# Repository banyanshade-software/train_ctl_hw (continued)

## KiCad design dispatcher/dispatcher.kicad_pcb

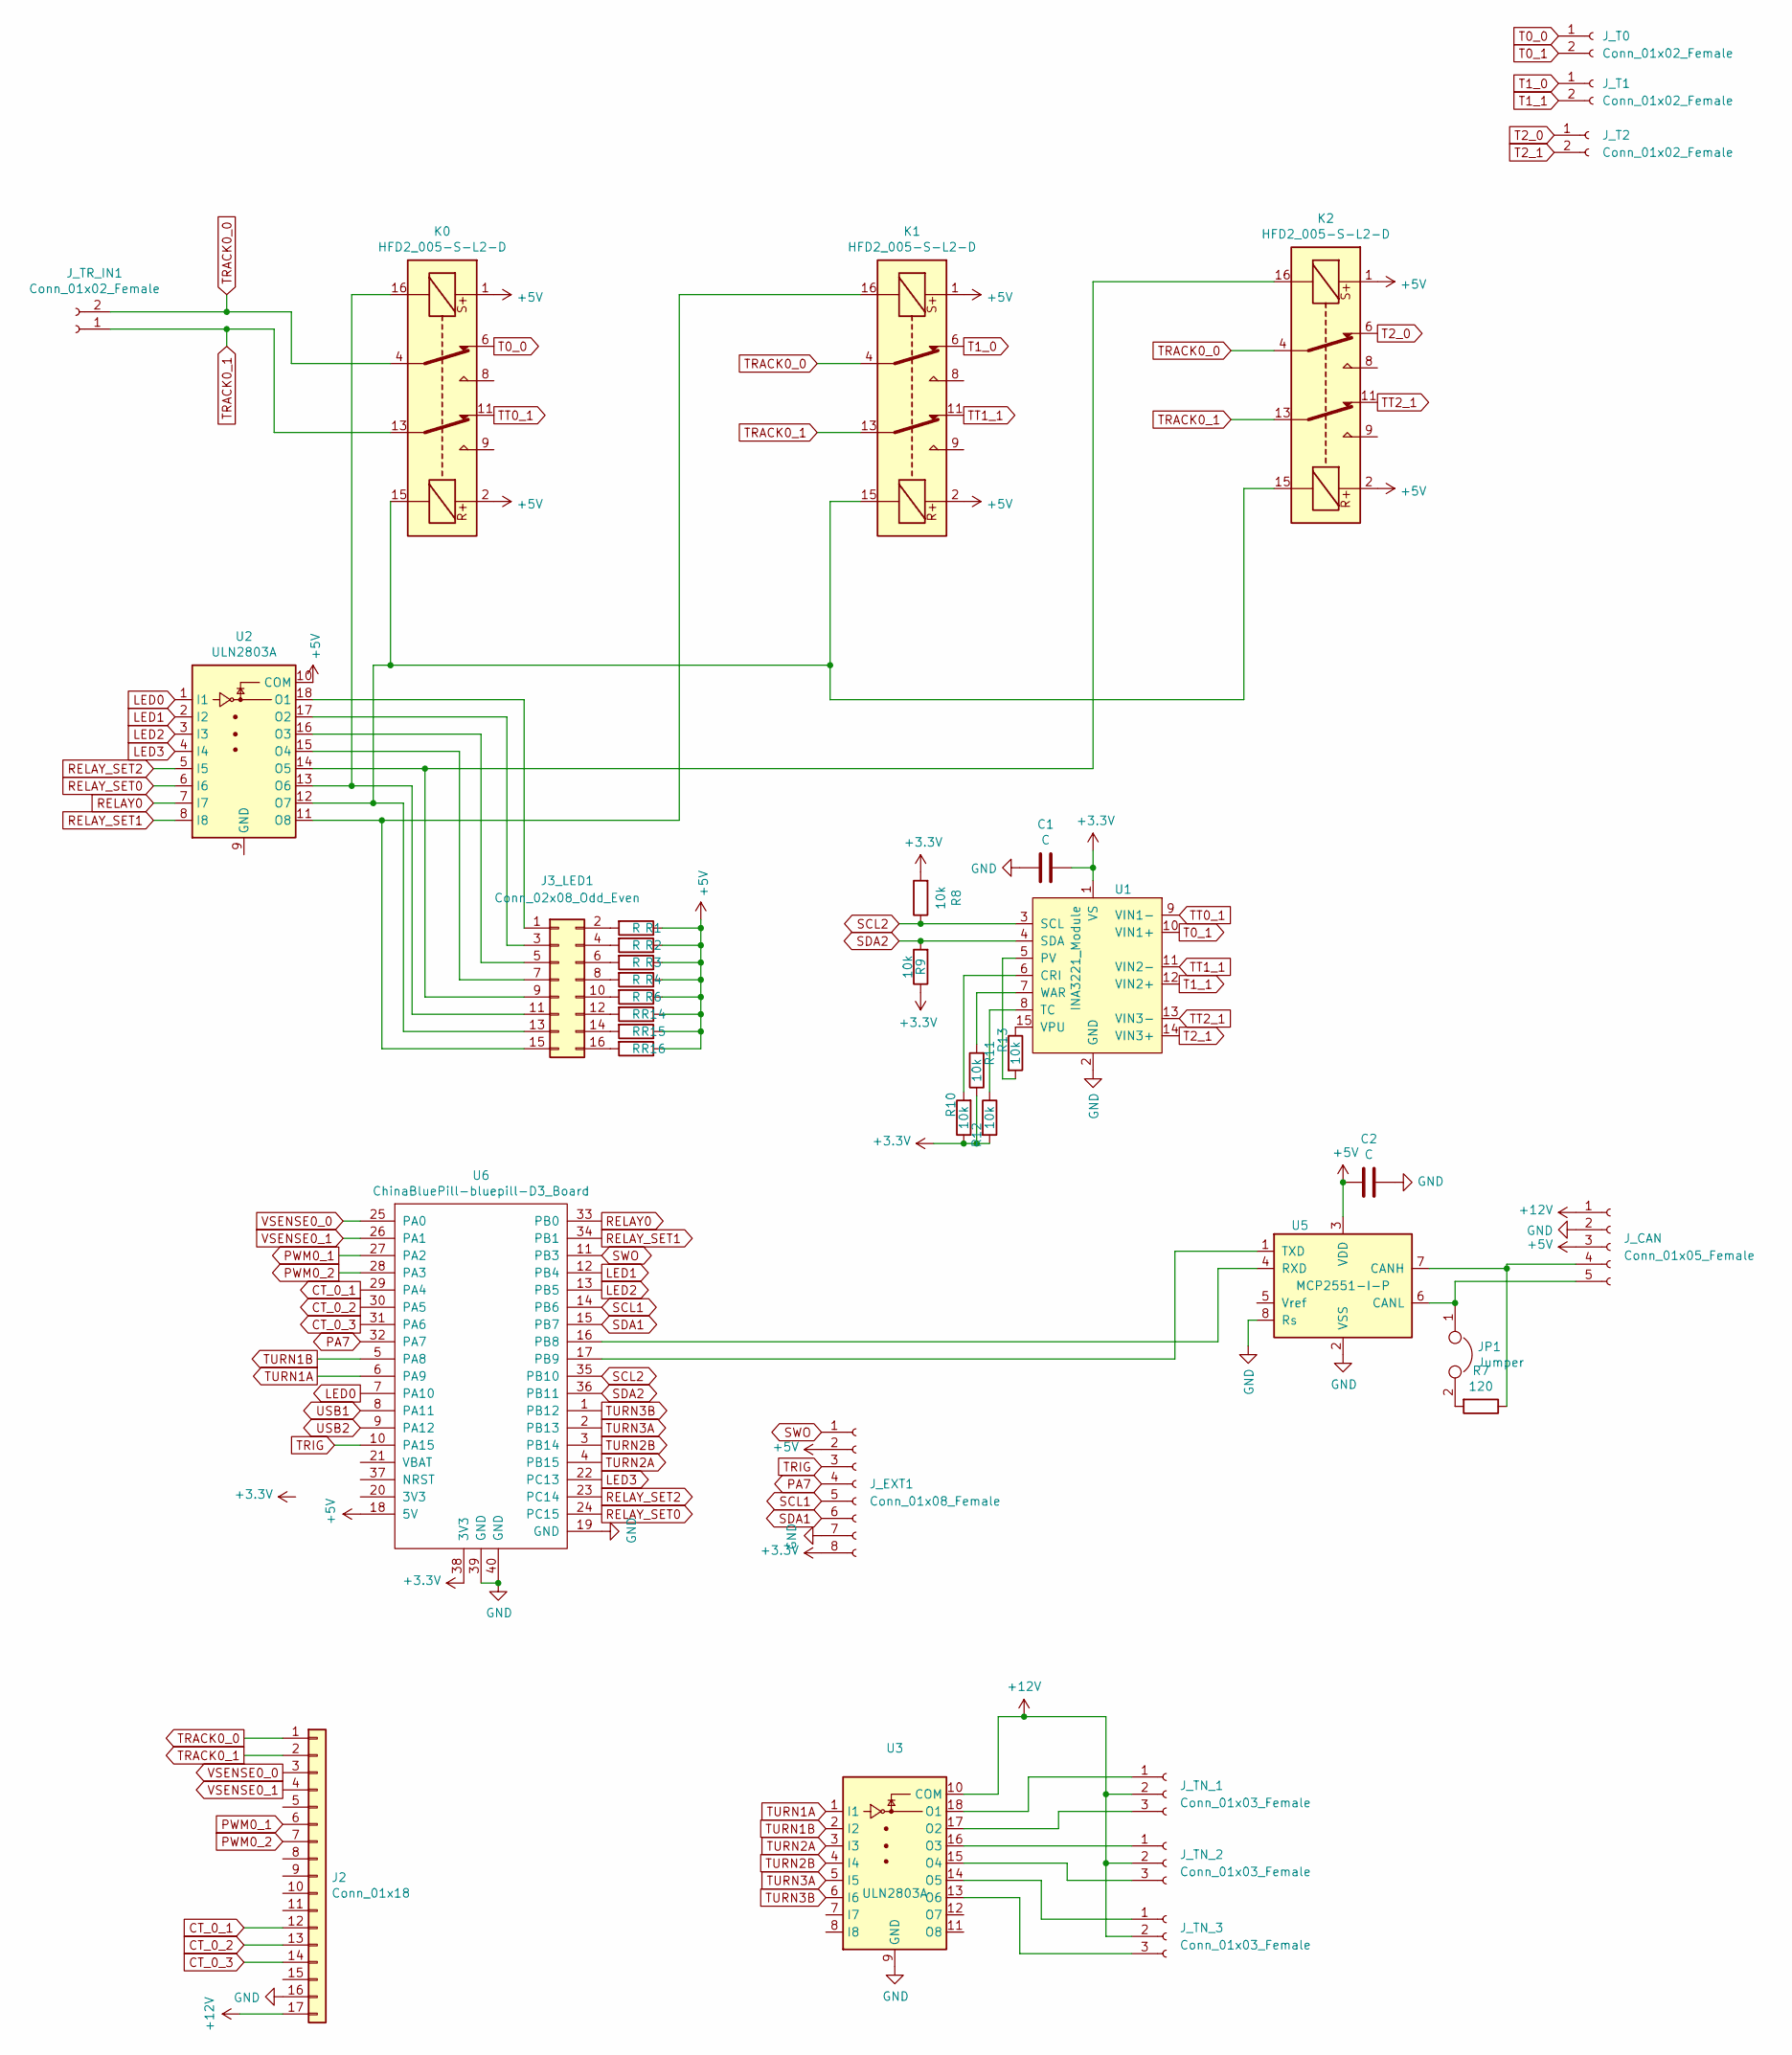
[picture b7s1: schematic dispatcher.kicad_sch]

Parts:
C1, C2: C; C_Disc_D3.4mm_W2.1mm_P2.50mm
J2: Conn_01x18; PinHeader_1x17_P2.54mm_Vertical
J3_LED1: Conn_02x08_Odd_Even; PinHeader_2x08_P2.54mm_Vertical
JP1: Jumper; PinHeader_1x02_P2.54mm_Vertical
J_CAN: Conn_01x05_Female; PinHeader_1x05_P2.54mm_Vertical
J_EXT1: Conn_01x08_Female; PinHeader_1x08_P2.54mm_Vertical
J_T0, J_T1, J_T2: Conn_01x02_Female; PinHeader_1x02_P2.54mm_Vertical
J_TN_1, J_TN_2, J_TN_3: Conn_01x03_Female; PinHeader_1x03_P2.54mm_Vertical
J_TR_IN1: Conn_01x02_Female; PinHeader_1x02_P2.54mm_Vertical
K0, K1, K2: HFD2_005-S-L2-D; HFD2-005-S-L2-D
R1, R2, R3, R4, R6, R14, R15, R16: R; R_Axial_DIN0207_L6.3mm_D2.5mm_P7.62mm_Horizontal
R7: 120; R_Axial_DIN0207_L6.3mm_D2.5mm_P7.62mm_Horizontal
R8, R9, R10, R11, R12, R13: 10k; R_Axial_DIN0207_L6.3mm_D2.5mm_P7.62mm_Horizontal
U1: INA3221_Module
U2, U3: ULN2803A; DIP-18_W7.62mm
U5: MCP2551-I-P; DIP-8_W7.62mm
U6: ChinaBluePill-bluepill-D3_Board; BluePill_STM32F103C

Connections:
+3V3: C1.1, J_EXT1.8, R8.2, R9.1, R10.1, R11.1, R12.2, U1.1 (VS), U6.38 (3V3)
+5V: C2.2, J_CAN.3, J_EXT1.2, K0.1, K0.2, K1.1, K1.2, K2.1, K2.2, R1.1, R2.1, R3.1, R4.1, R6.1, R14.1, R15.1, R16.1, U2.10 (COM), U5.3 (VDD), U6.18 (5V); also elsewhere on the board
+12V: J2.17, J_CAN.1, J_TN_1.2, J_TN_2.2, J_TN_3.2, U3.10 (COM); also elsewhere on the board
CT_0_1: J2.12, U6.29 (PA4)
CT_0_2: J2.13, U6.30 (PA5)
CT_0_3: J2.14, U6.31 (PA6)
GND: C1.2, C2.1, J2.16, J_CAN.2, J_EXT1.7, U1.2 (GND), U3.9 (GND), U5.2 (VSS), U5.8 (Rs), U6.19 (GND), U6.39 (GND), U6.40 (GND); also elsewhere on the board
LED0: U2.1 (I1), U6.7 (PA10)
LED1: U2.2 (I2), U6.12 (PB4)
LED2: U2.3 (I3), U6.13 (PB5)
LED3: U2.4 (I4), U6.22 (PC13)
unnamed: J3_LED1.1, U2.18 (O1)
unnamed: J3_LED1.2, R1.2
unnamed: J3_LED1.3, U2.17 (O2)
unnamed: J3_LED1.4, R2.2
unnamed: J3_LED1.5, U2.16 (O3)
unnamed: J3_LED1.6, R3.2
unnamed: J3_LED1.7, U2.15 (O4)
unnamed: J3_LED1.8, R4.2
unnamed: J3_LED1.9, K2.16, U2.14 (O5)
unnamed: J3_LED1.10, R6.2
unnamed: J3_LED1.11, K0.16, U2.13 (O6)
unnamed: J3_LED1.12, R14.2
unnamed: J3_LED1.13, K0.15, K1.15, K2.15, U2.12 (O7)
unnamed: J3_LED1.14, R15.2
unnamed: J3_LED1.15, K1.16, U2.11 (O8)
unnamed: J3_LED1.16, R16.2
unnamed: JP1.2, R7.2
unnamed 28: JP1.1, J_CAN.5, U5.6 (CANL); also elsewhere on the board
unnamed: J_TN_1.1, U3.18 (O1)
unnamed: J_TN_1.3, U3.17 (O2)
unnamed: J_TN_2.1, U3.16 (O3)
unnamed: J_TN_2.3, U3.15 (O4)
unnamed: J_TN_3.1, U3.14 (O5)
unnamed: J_TN_3.3, U3.13 (O6)
unnamed 35: J_CAN.4, R7.1, U5.7 (CANH); also elsewhere on the board
unnamed: R10.2, U1.6 (CRI)
unnamed: R11.2, U1.7 (WAR)
unnamed: R12.1, U1.8 (TC)
unnamed: R13.1, U1.15 (VPU)
unnamed: R13.2, U1.5 (PV)
unnamed: U5.1 (TXD), U6.17 (PB9)
unnamed: U5.4 (RXD), U6.16 (PB8)
PA7: J_EXT1.4, U6.32 (PA7)
PWM0_1: J2.6, U6.27 (PA2)
PWM0_2: J2.7, U6.28 (PA3)
RELAY0: U2.7 (I7), U6.33 (PB0)
RELAY_SET0: U2.6 (I6), U6.24 (PC15)
RELAY_SET1: U2.8 (I8), U6.34 (PB1)
RELAY_SET2: U2.5 (I5), U6.23 (PC14)
SCL1: J_EXT1.5, U6.14 (PB6)
SCL2: R8.1, U1.3 (SCL), U6.35 (PB10)
SDA1: J_EXT1.6, U6.15 (PB7)
SDA2: R9.2, U1.4 (SDA), U6.36 (PB11)
SWO: J_EXT1.1, U6.11 (PB3)
T0_0: J_T0.1, K0.6
T0_1: J_T0.2, U1.10 (VIN1+)
T1_0: J_T1.1, K1.6
T1_1: J_T1.2, U1.12 (VIN2+)
T2_0: J_T2.1, K2.6
T2_1: J_T2.2, U1.14 (VIN3+)
TRACK0_0: J2.1, J_TR_IN1.2, K0.4, K1.4, K2.4
TRACK0_1: J2.2, J_TR_IN1.1, K0.13, K1.13, K2.13
TRIG: J_EXT1.3, U6.10 (PA15)
TT0_1: K0.11, U1.9 (VIN1-)
TT1_1: K1.11, U1.11 (VIN2-)
TT2_1: K2.11, U1.13 (VIN3-)
TURN1A: U3.1 (I1), U6.6 (PA9)
TURN1B: U3.2 (I2), U6.5 (PA8)
TURN2A: U3.3 (I3), U6.4 (PB15)
TURN2B: U3.4 (I4), U6.3 (PB14)
TURN3A: U3.5 (I5), U6.2 (PB13)
TURN3B: U3.6 (I6), U6.1 (PB12)
USB1: U6.8 (PA11)
USB2: U6.9 (PA12)
VSENSE0_0: J2.3, U6.25 (PA0)
VSENSE0_1: J2.4, U6.26 (PA1)

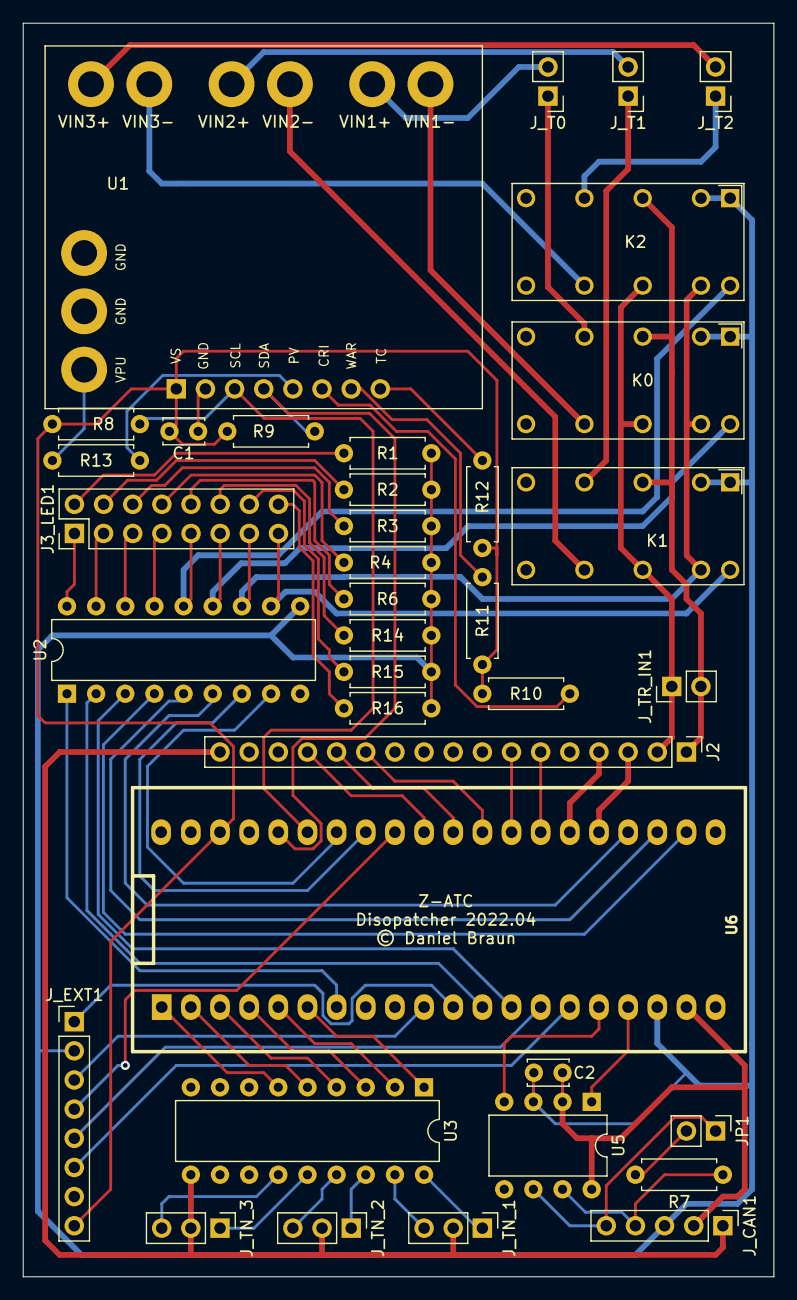
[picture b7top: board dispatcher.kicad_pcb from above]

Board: 2 copper layers, 65.4 x 109.2 mm, 37 parts (0 on the bottom side), 75 nets.

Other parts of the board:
J_CAN1: Conn_01x05_Female; PinHeader_1x05_P2.54mm_Vertical

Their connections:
+5V: J_CAN1.3; also elsewhere on the board
+12V: J_CAN1.1; also elsewhere on the board
GND: J_CAN1.2; also elsewhere on the board
unnamed 28: J_CAN1.5; also elsewhere on the board
unnamed 35: J_CAN1.4; also elsewhere on the board

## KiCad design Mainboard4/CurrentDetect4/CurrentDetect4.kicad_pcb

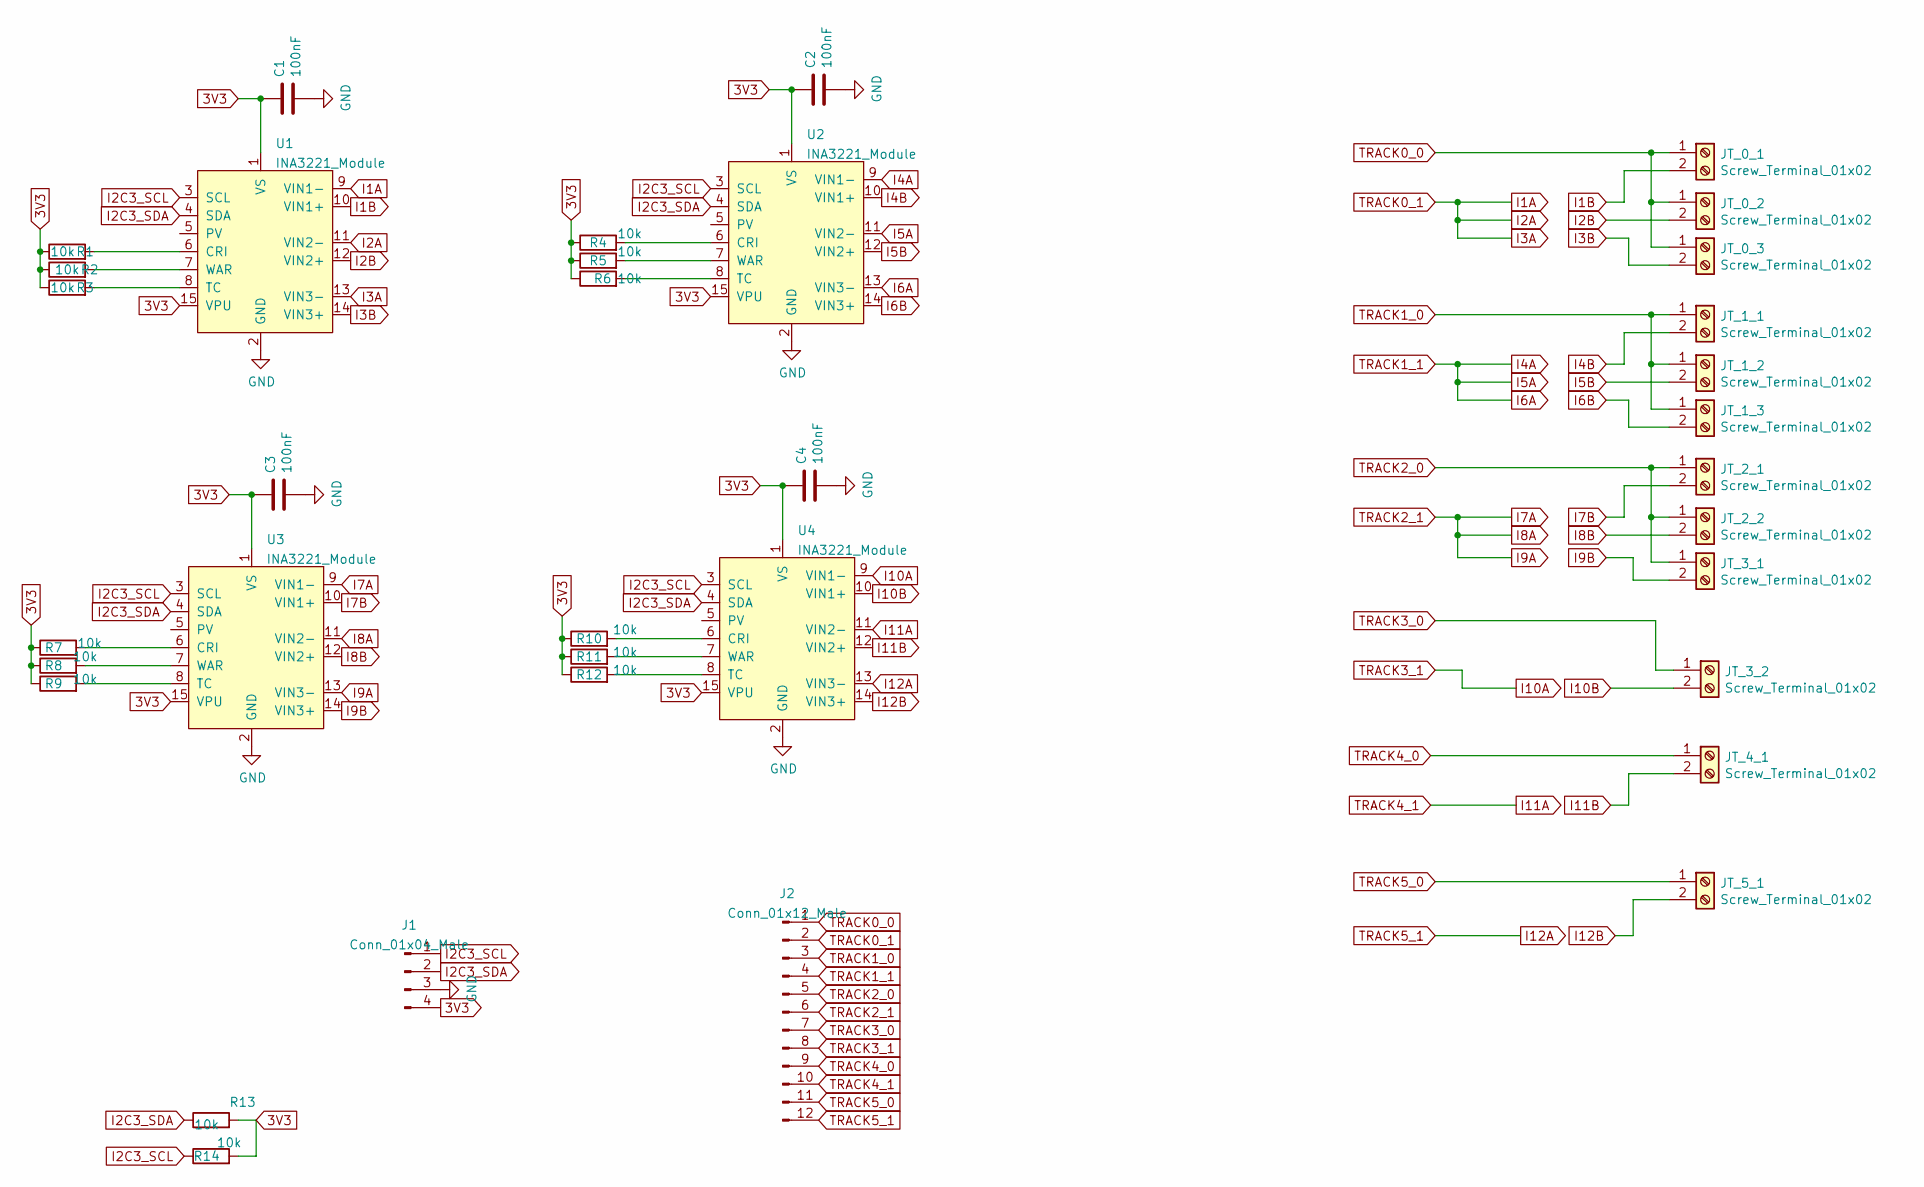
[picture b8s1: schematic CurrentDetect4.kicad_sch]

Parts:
C1, C2, C3, C4: 100nF; C_Disc_D3.4mm_W2.1mm_P2.50mm
J1: Conn_01x04_Male; PinHeader_1x04_P2.54mm_Vertical
J2: Conn_01x12_Male; PinHeader_1x12_P2.54mm_Vertical
JT_0_1, JT_0_2, JT_0_3, JT_1_1, JT_1_2, JT_1_3, JT_2_1, JT_2_2, JT_3_1, JT_3_2, JT_4_1, JT_5_1: Screw_Terminal_01x02; PinHeader_1x02_P2.54mm_Vertical
R1, R2, R3, R4, R5, R6, R7, R8, R9, R10, R11, R12, R13, R14: 10k; R_Axial_DIN0207_L6.3mm_D2.5mm_P7.62mm_Horizontal
U1, U2, U3, U4: INA3221_Module

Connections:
3V3: C1.2, C2.2, C3.2, C4.2, J1.4, R1.1, R2.1, R3.1, R4.1, R5.1, R6.1, R7.1, R8.1, R9.1, R10.1, R11.1, R12.1, R13.2, R14.2, U1.1 (VS), U1.15 (VPU), U2.1 (VS), U2.15 (VPU), U3.1 (VS), U3.15 (VPU), U4.1 (VS), U4.15 (VPU)
GND: C1.1, C2.1, C3.1, C4.1, J1.3, U1.2 (GND), U2.2 (GND), U3.2 (GND), U4.2 (GND)
I1A: J2.2, U1.9 (VIN1-), U1.11 (VIN2-), U1.13 (VIN3-)
I1B: JT_0_1.2, U1.10 (VIN1+)
I2B: JT_0_2.2, U1.12 (VIN2+)
I2C3_SCL: J1.1, R14.1, U1.3 (SCL), U2.3 (SCL), U3.3 (SCL), U4.3 (SCL)
I2C3_SDA: J1.2, R13.1, U1.4 (SDA), U2.4 (SDA), U3.4 (SDA), U4.4 (SDA)
I3B: JT_0_3.2, U1.14 (VIN3+)
I4A: J2.4, U2.9 (VIN1-), U2.11 (VIN2-), U2.13 (VIN3-)
I4B: JT_1_1.2, U2.10 (VIN1+)
I5B: JT_1_2.2, U2.12 (VIN2+)
I6B: JT_1_3.2, U2.14 (VIN3+)
I7A: J2.6, U3.9 (VIN1-), U3.11 (VIN2-), U3.13 (VIN3-)
I7B: JT_2_1.2, U3.10 (VIN1+)
I8B: JT_2_2.2, U3.12 (VIN2+)
I9B: JT_3_1.2, U3.14 (VIN3+)
I10A: J2.8, U4.9 (VIN1-)
I10B: JT_3_2.2, U4.10 (VIN1+)
I11A: J2.10, U4.11 (VIN2-)
I11B: JT_4_1.2, U4.12 (VIN2+)
I12A: J2.12, U4.13 (VIN3-)
I12B: JT_5_1.2, U4.14 (VIN3+)
unnamed: R1.2, U1.6 (CRI)
unnamed: R2.2, U1.7 (WAR)
unnamed: R3.2, U1.8 (TC)
unnamed: R4.2, U2.6 (CRI)
unnamed: R5.2, U2.7 (WAR)
unnamed: R6.2, U2.8 (TC)
unnamed: R7.2, U3.6 (CRI)
unnamed: R8.2, U3.7 (WAR)
unnamed: R9.2, U3.8 (TC)
unnamed: R10.2, U4.6 (CRI)
unnamed: R11.2, U4.7 (WAR)
unnamed: R12.2, U4.8 (TC)
TRACK0_0: J2.1, JT_0_1.1, JT_0_2.1, JT_0_3.1
TRACK1_0: J2.3, JT_1_1.1, JT_1_2.1, JT_1_3.1
TRACK2_0: J2.5, JT_2_1.1, JT_2_2.1, JT_3_1.1
TRACK3_0: J2.7, JT_3_2.1
TRACK4_0: J2.9, JT_4_1.1
TRACK5_0: J2.11, JT_5_1.1

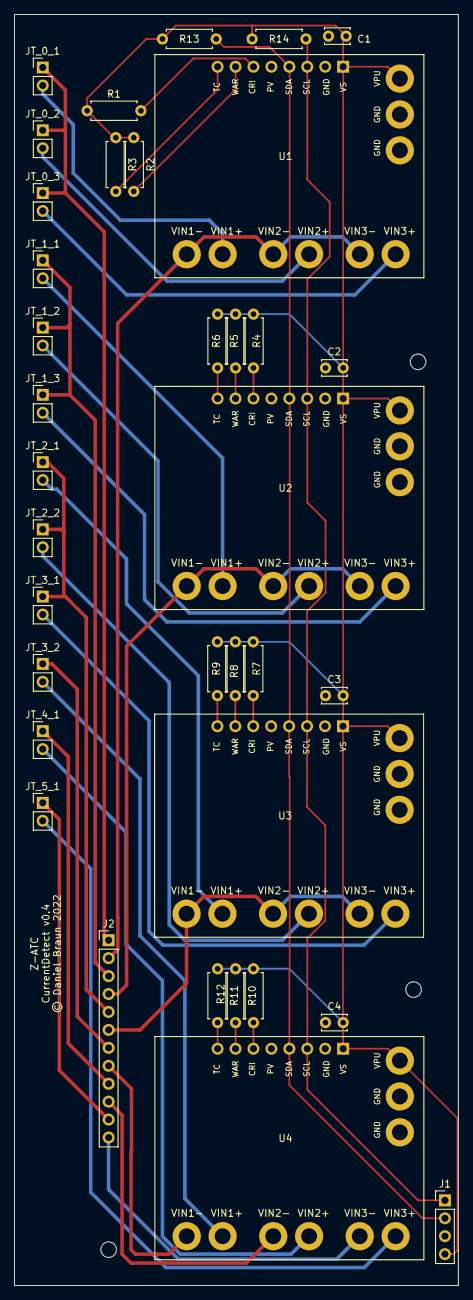
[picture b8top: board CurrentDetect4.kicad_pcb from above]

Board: 2 copper layers, 62.9 x 180.0 mm, 36 parts (0 on the bottom side), 40 nets.

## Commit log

2020-10-26 added files
2020-10-27 schematics
2020-11-13 moving to v2
2021-09-05 pcb canton3
2021-12-17 adding CAN interface
2021-12-17 adding dispatcher board
2021-12-23 mainboard3 again
2021-12-28 mainboard3 routing
2022-01-04 before moving to kicad6
2022-01-15 mainboard4 with kicad6
2022-01-16 nearly ok
2022-04-02 mainboard4 ready for production
2022-04-03 updated dispatcher
2022-04-06 updated to have full USB and external flash
2022-04-06 add switcher board, derived from dispatcher
2022-04-06 update switcher board, DRC OK
2023-07-16 add template and shield from templates
2023-12-29 updated libs for kicad7
2023-12-29 updated template
2023-12-29 add G4Lib
2023-12-29 misc update
2023-12-29 moved old versions
2023-12-29 moved to obsolete
2024-01-03 updated template and specs for G4
2024-01-07 update spec
2024-01-07 update spec with relay use cases
2024-01-07 update spec J_TRACK and mapping
2024-01-07 update spec POW_CTRL
2024-01-07 add 74HC794
2024-01-07 add G4_Switch, on progress
2024-01-07 updated G4_Switch
2024-01-08 updated G4_Switch, DRC run ok
2024-01-10 add in G4Lib: INA3221, G491RE20
2024-01-10 add G4_Current module, with first routing attempt
2024-01-10 fix some connectors
2024-01-10 change i2c1 and i2c3 for better routing
